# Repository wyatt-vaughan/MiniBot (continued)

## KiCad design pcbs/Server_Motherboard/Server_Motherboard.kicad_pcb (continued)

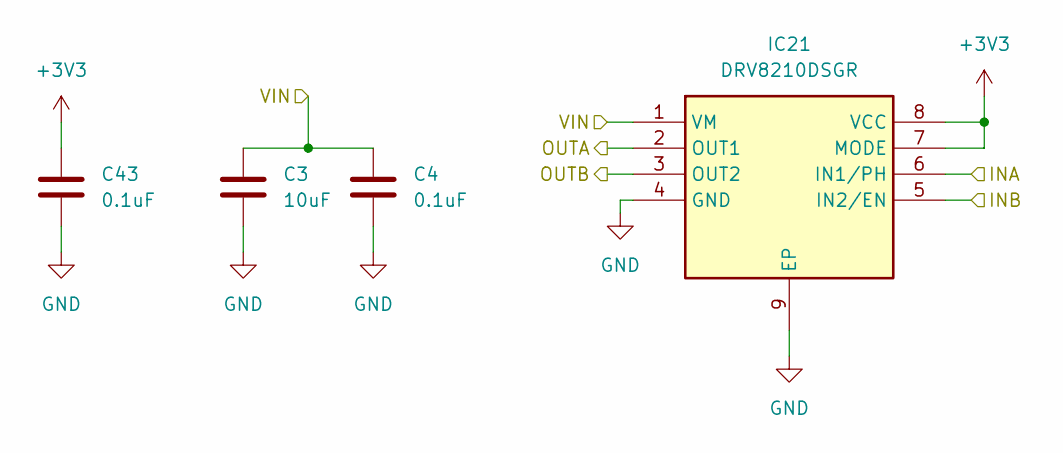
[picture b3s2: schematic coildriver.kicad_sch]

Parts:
C3: 10uF; C_0603_1608Metric
C4, C43: 0.1uF; C_0402_1005Metric
IC21: DRV8210DSGR; SON50P200X200X80-9N; Mouser Part Number 595-DRV8210DSGR

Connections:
+3V3: C43.1, IC21.7 (MODE), IC21.8 (VCC); also elsewhere on the board
/COIL0_A: IC21.2 (OUT1); also elsewhere on the board
/COIL0_B: IC21.3 (OUT2); also elsewhere on the board
/COIL_DIR: IC21.6 (IN1/PH); also elsewhere on the board
/C_EN_0: IC21.5 (IN2/EN); also elsewhere on the board
GND: C3.2, C4.2, C43.2, IC21.4 (GND), IC21.9 (EP); also elsewhere on the board
VDC: C3.1, C4.1, IC21.1 (VM); also elsewhere on the board

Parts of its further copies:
C5, C7, C9, C11, C13, C15, C17, C19, C21, C23, C25, C27, C29, C31, C33, C35, C37, C39, C41: 10uF; C_0603_1608Metric
C6, C8, C10, C12, C14, C16, C18, C20, C22, C24, C26, C28, C30, C32, C34, C36, C38, C40, C42, C44, C45, C46, C47, C48, C49, C50, C51, C52, C53, C54, C55, C56, C57, C58, C59, C60, C61, C62: 0.1uF; C_0402_1005Metric
IC22, IC23, IC24, IC25, IC26, IC27, IC28, IC29, IC30, IC31, IC32, IC33, IC34, IC35, IC36, IC37, IC38, IC39, IC40: DRV8210DSGR; SON50P200X200X80-9N; Mouser Part Number 595-DRV8210DSGR

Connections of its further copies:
+3V3: C44.1, C45.1, C46.1, C47.1, C48.1, C49.1, C50.1, C51.1, C52.1, C53.1, C54.1, C55.1, C56.1, C57.1, C58.1, C59.1, C60.1, C61.1, C62.1, IC22.7 (MODE), IC22.8 (VCC), IC23.7 (MODE), IC23.8 (VCC), IC24.7 (MODE), IC24.8 (VCC), IC25.7 (MODE), IC25.8 (VCC), IC26.7 (MODE), IC26.8 (VCC), IC27.7 (MODE), IC27.8 (VCC), IC28.7 (MODE), IC28.8 (VCC), IC29.7 (MODE), IC29.8 (VCC), IC30.7 (MODE), IC30.8 (VCC), IC31.7 (MODE), IC31.8 (VCC), IC32.7 (MODE), IC32.8 (VCC), IC33.7 (MODE), IC33.8 (VCC), IC34.7 (MODE), IC34.8 (VCC), IC35.7 (MODE), IC35.8 (VCC), IC36.7 (MODE), IC36.8 (VCC), IC37.7 (MODE), IC37.8 (VCC), IC38.7 (MODE), IC38.8 (VCC), IC39.7 (MODE), IC39.8 (VCC), IC40.7 (MODE), IC40.8 (VCC); also elsewhere on the board
/COIL1_A: IC22.2 (OUT1); also elsewhere on the board
/COIL1_B: IC22.3 (OUT2); also elsewhere on the board
/COIL2_A: IC23.2 (OUT1); also elsewhere on the board
/COIL2_B: IC23.3 (OUT2); also elsewhere on the board
/COIL3_A: IC24.2 (OUT1); also elsewhere on the board
/COIL3_B: IC24.3 (OUT2); also elsewhere on the board
/COIL4_A: IC25.2 (OUT1); also elsewhere on the board
/COIL4_B: IC25.3 (OUT2); also elsewhere on the board
/COIL5_A: IC26.2 (OUT1); also elsewhere on the board
/COIL5_B: IC26.3 (OUT2); also elsewhere on the board
/COIL6_A: IC27.2 (OUT1); also elsewhere on the board
/COIL6_B: IC27.3 (OUT2); also elsewhere on the board
/COIL7_A: IC28.2 (OUT1); also elsewhere on the board
/COIL7_B: IC28.3 (OUT2); also elsewhere on the board
/COIL8_A: IC29.2 (OUT1); also elsewhere on the board
/COIL8_B: IC29.3 (OUT2); also elsewhere on the board
/COIL9_A: IC30.2 (OUT1); also elsewhere on the board
/COIL9_B: IC30.3 (OUT2); also elsewhere on the board
/COIL10_A: IC31.2 (OUT1); also elsewhere on the board
/COIL10_B: IC31.3 (OUT2); also elsewhere on the board
/COIL11_A: IC32.2 (OUT1); also elsewhere on the board
/COIL11_B: IC32.3 (OUT2); also elsewhere on the board
/COIL12_A: IC33.2 (OUT1); also elsewhere on the board
/COIL12_B: IC33.3 (OUT2); also elsewhere on the board
/COIL13_A: IC34.2 (OUT1); also elsewhere on the board
/COIL13_B: IC34.3 (OUT2); also elsewhere on the board
/COIL14_A: IC35.2 (OUT1); also elsewhere on the board
/COIL14_B: IC35.3 (OUT2); also elsewhere on the board
/COIL15_A: IC36.2 (OUT1); also elsewhere on the board
/COIL15_B: IC36.3 (OUT2); also elsewhere on the board
/COIL16_A: IC37.2 (OUT1); also elsewhere on the board
/COIL16_B: IC37.3 (OUT2); also elsewhere on the board
/COIL17_A: IC38.2 (OUT1); also elsewhere on the board
/COIL17_B: IC38.3 (OUT2); also elsewhere on the board
/COIL18_A: IC39.2 (OUT1); also elsewhere on the board
/COIL18_B: IC39.3 (OUT2); also elsewhere on the board
/COIL19_A: IC40.2 (OUT1); also elsewhere on the board
/COIL19_B: IC40.3 (OUT2); also elsewhere on the board
/COIL_DIR: IC22.6 (IN1/PH), IC23.6 (IN1/PH), IC24.6 (IN1/PH), IC25.6 (IN1/PH), IC26.6 (IN1/PH), IC27.6 (IN1/PH), IC28.6 (IN1/PH), IC29.6 (IN1/PH), IC30.6 (IN1/PH), IC31.6 (IN1/PH), IC32.6 (IN1/PH), IC33.6 (IN1/PH), IC34.6 (IN1/PH), IC35.6 (IN1/PH), IC36.6 (IN1/PH), IC37.6 (IN1/PH), IC38.6 (IN1/PH), IC39.6 (IN1/PH), IC40.6 (IN1/PH); also elsewhere on the board
/C_EN_1: IC22.5 (IN2/EN); also elsewhere on the board
/C_EN_2: IC23.5 (IN2/EN); also elsewhere on the board
/C_EN_3: IC24.5 (IN2/EN); also elsewhere on the board
/C_EN_4: IC25.5 (IN2/EN); also elsewhere on the board
/C_EN_5: IC26.5 (IN2/EN); also elsewhere on the board
/C_EN_6: IC27.5 (IN2/EN); also elsewhere on the board
/C_EN_7: IC28.5 (IN2/EN); also elsewhere on the board
/C_EN_8: IC29.5 (IN2/EN); also elsewhere on the board
/C_EN_9: IC30.5 (IN2/EN); also elsewhere on the board
/C_EN_10: IC31.5 (IN2/EN); also elsewhere on the board
/C_EN_11: IC32.5 (IN2/EN); also elsewhere on the board
/C_EN_12: IC33.5 (IN2/EN); also elsewhere on the board
/C_EN_13: IC34.5 (IN2/EN); also elsewhere on the board
/C_EN_14: IC35.5 (IN2/EN); also elsewhere on the board
/C_EN_15: IC36.5 (IN2/EN); also elsewhere on the board
/C_EN_16: IC37.5 (IN2/EN); also elsewhere on the board
/C_EN_17: IC38.5 (IN2/EN); also elsewhere on the board
/C_EN_18: IC39.5 (IN2/EN); also elsewhere on the board
/C_EN_19: IC40.5 (IN2/EN); also elsewhere on the board
GND: C5.2, C6.2, C7.2, C8.2, C9.2, C10.2, C11.2, C12.2, C13.2, C14.2, C15.2, C16.2, C17.2, C18.2, C19.2, C20.2, C21.2, C22.2, C23.2, C24.2, C25.2, C26.2, C27.2, C28.2, C29.2, C30.2, C31.2, C32.2, C33.2, C34.2, C35.2, C36.2, C37.2, C38.2, C39.2, C40.2, C41.2, C42.2, C44.2, C45.2, C46.2, C47.2, C48.2, C49.2, C50.2, C51.2, C52.2, C53.2, C54.2, C55.2, C56.2, C57.2, C58.2, C59.2, C60.2, C61.2, C62.2, IC22.4 (GND), IC22.9 (EP), IC23.4 (GND), IC23.9 (EP), IC24.4 (GND), IC24.9 (EP), IC25.4 (GND), IC25.9 (EP), IC26.4 (GND), IC26.9 (EP), IC27.4 (GND), IC27.9 (EP), IC28.4 (GND), IC28.9 (EP), IC29.4 (GND), IC29.9 (EP), IC30.4 (GND), IC30.9 (EP), IC31.4 (GND), IC31.9 (EP), IC32.4 (GND), IC32.9 (EP), IC33.4 (GND), IC33.9 (EP), IC34.4 (GND), IC34.9 (EP), IC35.4 (GND), IC35.9 (EP), IC36.4 (GND), IC36.9 (EP), IC37.4 (GND), IC37.9 (EP), IC38.4 (GND), IC38.9 (EP), IC39.4 (GND), IC39.9 (EP), IC40.4 (GND), IC40.9 (EP); also elsewhere on the board
VDC: C5.1, C6.1, C7.1, C8.1, C9.1, C10.1, C11.1, C12.1, C13.1, C14.1, C15.1, C16.1, C17.1, C18.1, C19.1, C20.1, C21.1, C22.1, C23.1, C24.1, C25.1, C26.1, C27.1, C28.1, C29.1, C30.1, C31.1, C32.1, C33.1, C34.1, C35.1, C36.1, C37.1, C38.1, C39.1, C40.1, C41.1, C42.1, IC22.1 (VM), IC23.1 (VM), IC24.1 (VM), IC25.1 (VM), IC26.1 (VM), IC27.1 (VM), IC28.1 (VM), IC29.1 (VM), IC30.1 (VM), IC31.1 (VM), IC32.1 (VM), IC33.1 (VM), IC34.1 (VM), IC35.1 (VM), IC36.1 (VM), IC37.1 (VM), IC38.1 (VM), IC39.1 (VM), IC40.1 (VM); also elsewhere on the board

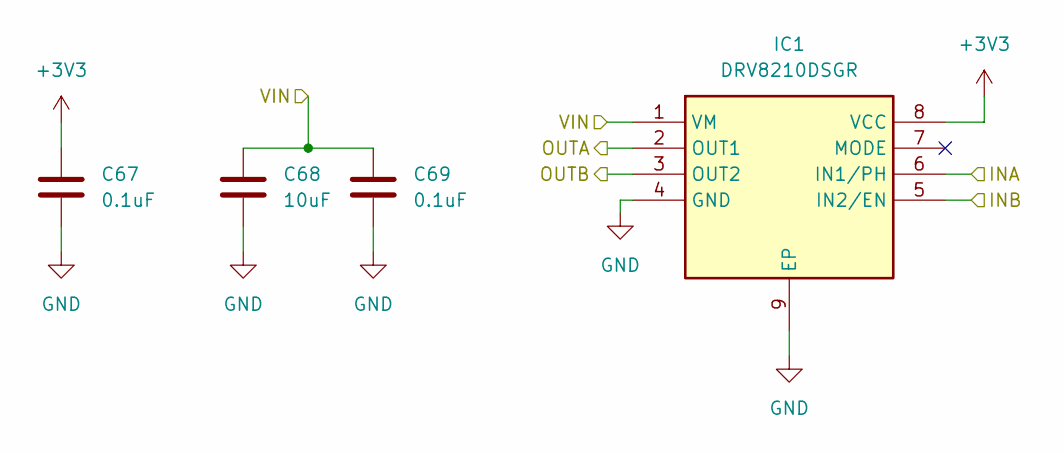
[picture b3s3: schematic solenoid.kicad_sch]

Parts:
C67, C69: 0.1uF; C_0402_1005Metric
C68: 10uF; C_0603_1608Metric
IC1: DRV8210DSGR; SON50P200X200X80-9N; Mouser Part Number 595-DRV8210DSGR

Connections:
+3V3: C67.1, IC1.8 (VCC); also elsewhere on the board
/SOL_0: IC1.3 (OUT2); also elsewhere on the board
/SOL_1: IC1.2 (OUT1); also elsewhere on the board
/SOL_EN_0: IC1.6 (IN1/PH); also elsewhere on the board
/SOL_EN_1: IC1.5 (IN2/EN); also elsewhere on the board
GND: C67.2, C68.2, C69.2, IC1.4 (GND), IC1.9 (EP); also elsewhere on the board
VDC: C68.1, C69.1, IC1.1 (VM); also elsewhere on the board

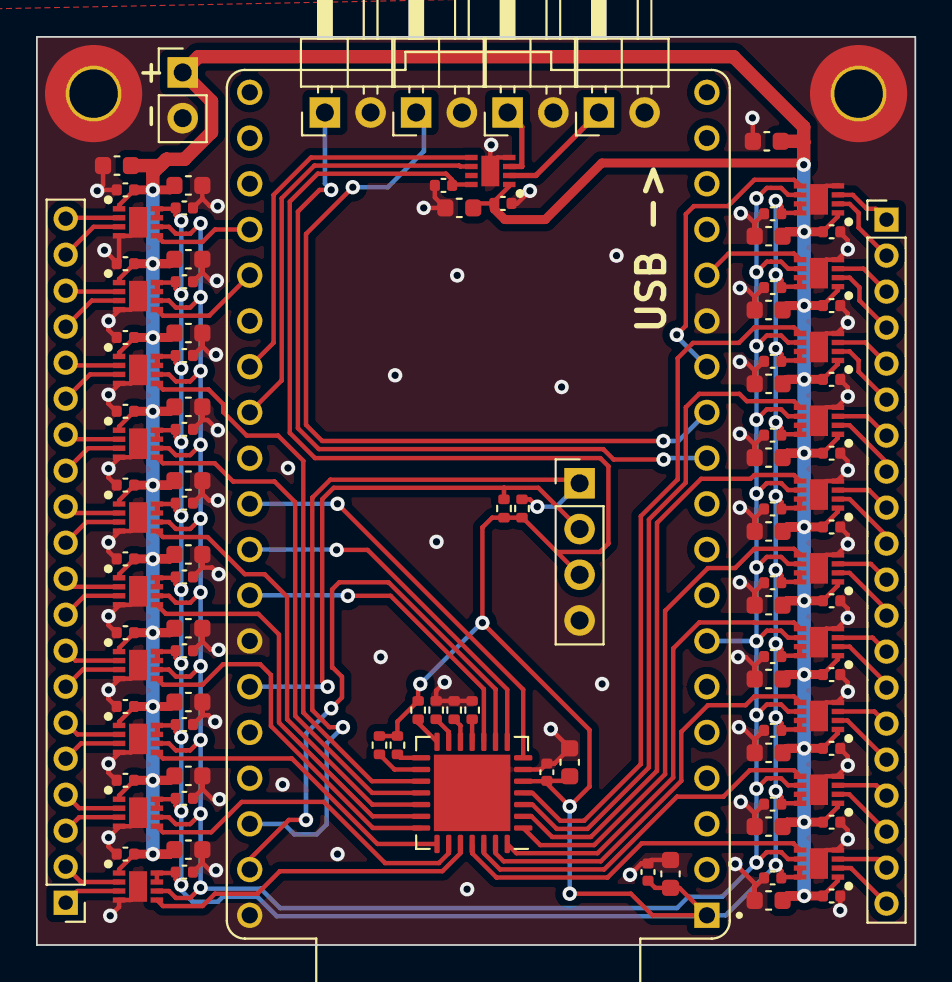
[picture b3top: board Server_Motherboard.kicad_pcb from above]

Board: 2 copper layers, 48.8 x 50.4 mm, 110 parts (0 on the bottom side), 82 nets.

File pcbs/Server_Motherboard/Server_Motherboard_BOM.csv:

"Id";"Designator";"Footprint";"Quantity";"Designation";"Supplier and ref";
1;"IC40,IC39,IC38,IC37,IC36,IC35,IC34,IC33,IC32,IC31,IC30,IC29,IC28,IC27,IC26,IC25,IC24,IC23,IC22,IC21,IC1";"SON50P200X200X80-9N";21;"DRV8210DSGR";;;
2;"C67,C12,C54,C24,C61,C45,C51,C59,C26,C40,C47,C52,C63,C34,C50,C4,C60,C10,C32,C43,C18,C14,C28,C8,C62,C42,C2,C49,C36,C16,C58,C57,C6,C38,C22,C46,C30,C56,C20,C69,C53,C55,C44,C48";"C_0402_1005Metric";44;"0.1uF";;;
3;"C5,C66,C65,C35,C37,C25,C19,C39,C31,C7,C11,C68,C15,C29,C17,C33,C9,C3,C13,C41,C21,C27,C64,C1,C23";"C_0603_1608Metric";25;"10uF";;;
4;"R7,R5,R8,R6,R1,R4,R3,R2";"R_0402_1005Metric";8;"10k";;;
5;"U2";"QFN-28-1EP_6x6mm_P0.65mm_EP4.25x4.25mm";1;"MCP23S17_ML";;;

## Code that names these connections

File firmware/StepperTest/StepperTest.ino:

#define M0_STEP 5
#define M0_DIR 4
#define M0_EN 6
#define M0_RST 7
#define M1_STEP 1
#define M1_DIR 10
#define M1_EN 0
#define M1_RST 3


void setup() {
  Serial.begin(115200);

  pinMode(M0_STEP, OUTPUT);
  pinMode(M0_DIR, OUTPUT);
  pinMode(M0_EN, OUTPUT);
  pinMode(M0_RST, OUTPUT);
  pinMode(M1_STEP, OUTPUT);
  pinMode(M1_DIR, OUTPUT);
  pinMode(M1_EN, OUTPUT);
  pinMode(M1_RST, OUTPUT);

  digitalWrite(M0_STEP, LOW);
  digitalWrite(M0_DIR, LOW);
  digitalWrite(M0_EN, LOW);
  digitalWrite(M0_RST, LOW);
  digitalWrite(M1_STEP, LOW);
  digitalWrite(M1_DIR, LOW);
  digitalWrite(M1_EN, LOW);
  digitalWrite(M1_RST, LOW);

  // Set microstepping to 1/256
  // digitalWrite(M0_STEP, LOW);
  // digitalWrite(M0_DIR, LOW);
  // digitalWrite(M1_STEP, LOW);
  // digitalWrite(M1_DIR, LOW);

  // Set microstepping to 1/8
  digitalWrite(M0_STEP, HIGH);
  digitalWrite(M0_DIR, LOW);
  digitalWrite(M1_STEP, HIGH);
  digitalWrite(M1_DIR, LOW);

  // Startup
  delay(20);
  digitalWrite(M0_RST, HIGH);
  digitalWrite(M1_RST, HIGH);

  delay(100);
  digitalWrite(M0_EN, HIGH);
  digitalWrite(M1_EN, HIGH);
}

void loop() {
  uint16_t stepdelay = 1200;
  digitalWrite(M0_DIR, LOW);
  digitalWrite(M1_DIR, LOW);
  for (uint16_t i = 0; i < 500; i++)
  {
    digitalWrite(M0_STEP, HIGH);
    digitalWrite(M1_STEP, HIGH);
    delayMicroseconds(stepdelay);
    digitalWrite(M0_STEP, LOW);
    digitalWrite(M1_STEP, LOW);
    delayMicroseconds(stepdelay);
  }

  digitalWrite(M0_EN, LOW);
  digitalWrite(M1_EN, LOW);
  delay(2000);
  digitalWrite(M0_EN, HIGH);
  digitalWrite(M1_EN, HIGH);

  digitalWrite(M0_DIR, HIGH);
  digitalWrite(M1_DIR, HIGH);
  for (uint16_t i = 0; i < 500; i++)
  {
    digitalWrite(M0_STEP, HIGH);
    digitalWrite(M1_STEP, HIGH);
    delayMicroseconds(stepdelay);
    digitalWrite(M0_STEP, LOW);
    digitalWrite(M1_STEP, LOW);
    delayMicroseconds(stepdelay);
  }

  digitalWrite(M0_EN, LOW);
  digitalWrite(M1_EN, LOW);
  delay(2000);
  digitalWrite(M0_EN, HIGH);
  digitalWrite(M1_EN, HIGH);

  digitalWrite(M0_DIR, HIGH);
  digitalWrite(M1_DIR, LOW);
  for (uint16_t i = 0; i < 500; i++)
  {
    digitalWrite(M0_STEP, HIGH);
    digitalWrite(M1_STEP, HIGH);
    delayMicroseconds(stepdelay);
    digitalWrite(M0_STEP, LOW);
    digitalWrite(M1_STEP, LOW);
    delayMicroseconds(stepdelay);
  }

  digitalWrite(M0_EN, LOW);
  digitalWrite(M1_EN, LOW);
  delay(2000);
  digitalWrite(M0_EN, HIGH);
  digitalWrite(M1_EN, HIGH);

  // GPIO.out_w1ts = ((uint32_t)1 << 22);
}

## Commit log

2025-10-14 big updates
2025-11-11 complete overhaul wip
2025-12-04 lots of pcb work, test code, and final fw framework starting
2025-12-08 big progress
2025-12-09 refining pcb and simulator code
2025-12-15 getting close to order state
2025-12-24 lots more progress
2025-12-31 checkpoint, wifi not working on client
2026-01-01 functional server-client model hooray
2026-01-02 reorg and write device ID to NVS
2026-02-14 push before I break everything
2026-02-26 checkpoint before i break everything
2026-03-26 testing coils, improved hall sensor integration, tons of cleanup
2026-03-26 some refactors, faster mag sensor reads, archived test code
2026-03-28 positioning alg done but not tested heheheheheh
2026-03-30 positioning kinda sorta works!
2026-04-03 some reorg, new coordinator app, improved positioning accuracy
2026-04-17 positioning improvements, sync changes
2026-04-18 positioning bugfixes, better sync
2026-04-22 debugged position estimator, cleanup old sync methods, clock drift demo
2026-04-24 move stepper object to dedicated file, integrate rmt functionality
2026-04-24 use RMT for cruise phase of rotation and linear moves
2026-04-24 RMT cruise debug, new timer based sensor acquisition
2026-04-30 maybe it will work, maybe it wont
2026-05-01 led updates
2026-05-01 improved pcb thermals
2026-05-01 readme updates
2026-05-01 split readme into sub-readmes
2026-05-04 cleanup minibot schematic
2026-05-07 try mermaid for readme
2026-05-08 some cleanup
2026-05-08 add command loop function to gui
2026-05-12 another bad path planner
2026-05-15 Checkpoint
2026-05-15 path planning still really janky but it kinda works
2026-05-15 multiprocessing path planning optimization
2026-05-16 stuff
2026-05-16 make looper betterrer
2026-05-18 Some optimizations
2026-05-29 add emag visualizer
2026-06-12 moving imported parts from my global dir to within this repo
2026-06-16 mostly finished server pcb, added pogo charge pins to bots, started charge case pcb
2026-06-19 Added basic FEN for setup.
2026-06-19 Added .gitignore
2026-06-19 Added GRAVEYARD_POSITIONS
2026-06-19 Added graveyard positions to set fen positions
2026-06-19 Moved HOME_POSITION of the 2 extra queens
2026-06-19 Added fixed height to _fen_input
2026-06-19 Added targeting for FEN string
2026-06-19 Added better documentation in code of new changes
2026-06-19 Removed testing planner for now
2026-06-20 gitignore and pcb updates
2026-06-20 remove ignored files
2026-06-20 remove kicad backups from repo
2026-06-21 begin work transitioning to hardware timer
2026-06-21 roadmap
2026-06-21 seems good enough probably still some edge case bugs
2026-06-21 cleanup
2026-06-21 BUG FIX: Changed fen error logging to use planning_log
2026-06-22 Added ability to manually move SIM pieces.
2026-06-22 Restore game and engine work
2026-06-22 Merged previous stash correctly.
2026-06-22 Removed random ignore folder
